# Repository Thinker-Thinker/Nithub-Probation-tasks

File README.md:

# Nithub-Probation-tasks
Contains Solution to NitHub Hardware Probation Tasks

author: Jokomba Quyum Adeola (THINKER)

Design and assemble a circuit using Arduino or Raspberry Pi to control an LED strip based on ambient light levels (use an LDR sensor).
Develop a PCB design (using KiCad or Eagle) for a temperature sensor module that communicates with the central hub.
Write firmware for an ESP32 to send sensor data (temperature, humidity) to a cloud server via MQTT.
Implement a security feature using a PIR motion sensor to trigger an alarm when motion is detected.
Optimize power consumption for a battery-powered IoT device by implementing sleep modes.

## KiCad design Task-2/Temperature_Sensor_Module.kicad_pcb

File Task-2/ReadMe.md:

Task 2 files

Develop a PCB design (using KiCad or Eagle) for a temperature sensor module that communicates with the central hub.

https://www.tinkercad.com/things/jzLXpQLUGEQ-nithub-task-2-

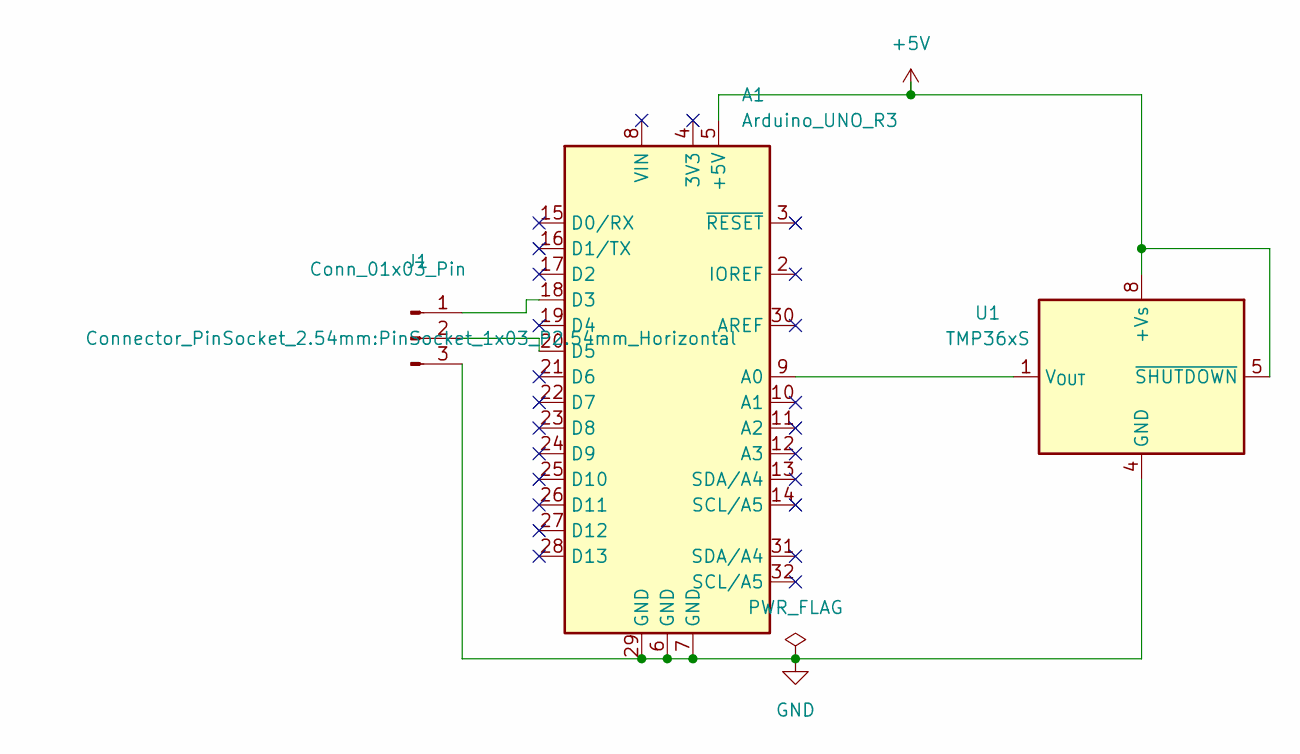
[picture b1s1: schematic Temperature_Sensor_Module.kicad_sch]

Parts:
A1: Arduino_UNO_R3
J1: Conn_01x03_Pin; PinSocket_1x03_P2.54mm_Horizontal
U1: TMP36xS; SOIC-8_3.9x4.9mm_P1.27mm

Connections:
+5V: A1.5 (+5V), U1.5 (~SHUTDOWN), U1.8 (+Vs)
GND: A1.6 (GND), A1.7 (GND), A1.29 (GND), J1.3, U1.4 (GND)
unnamed: A1.9 (A0), U1.1 (V_{OUT})
unnamed: A1.18 (D3), J1.1
unnamed: A1.20 (D5), J1.2

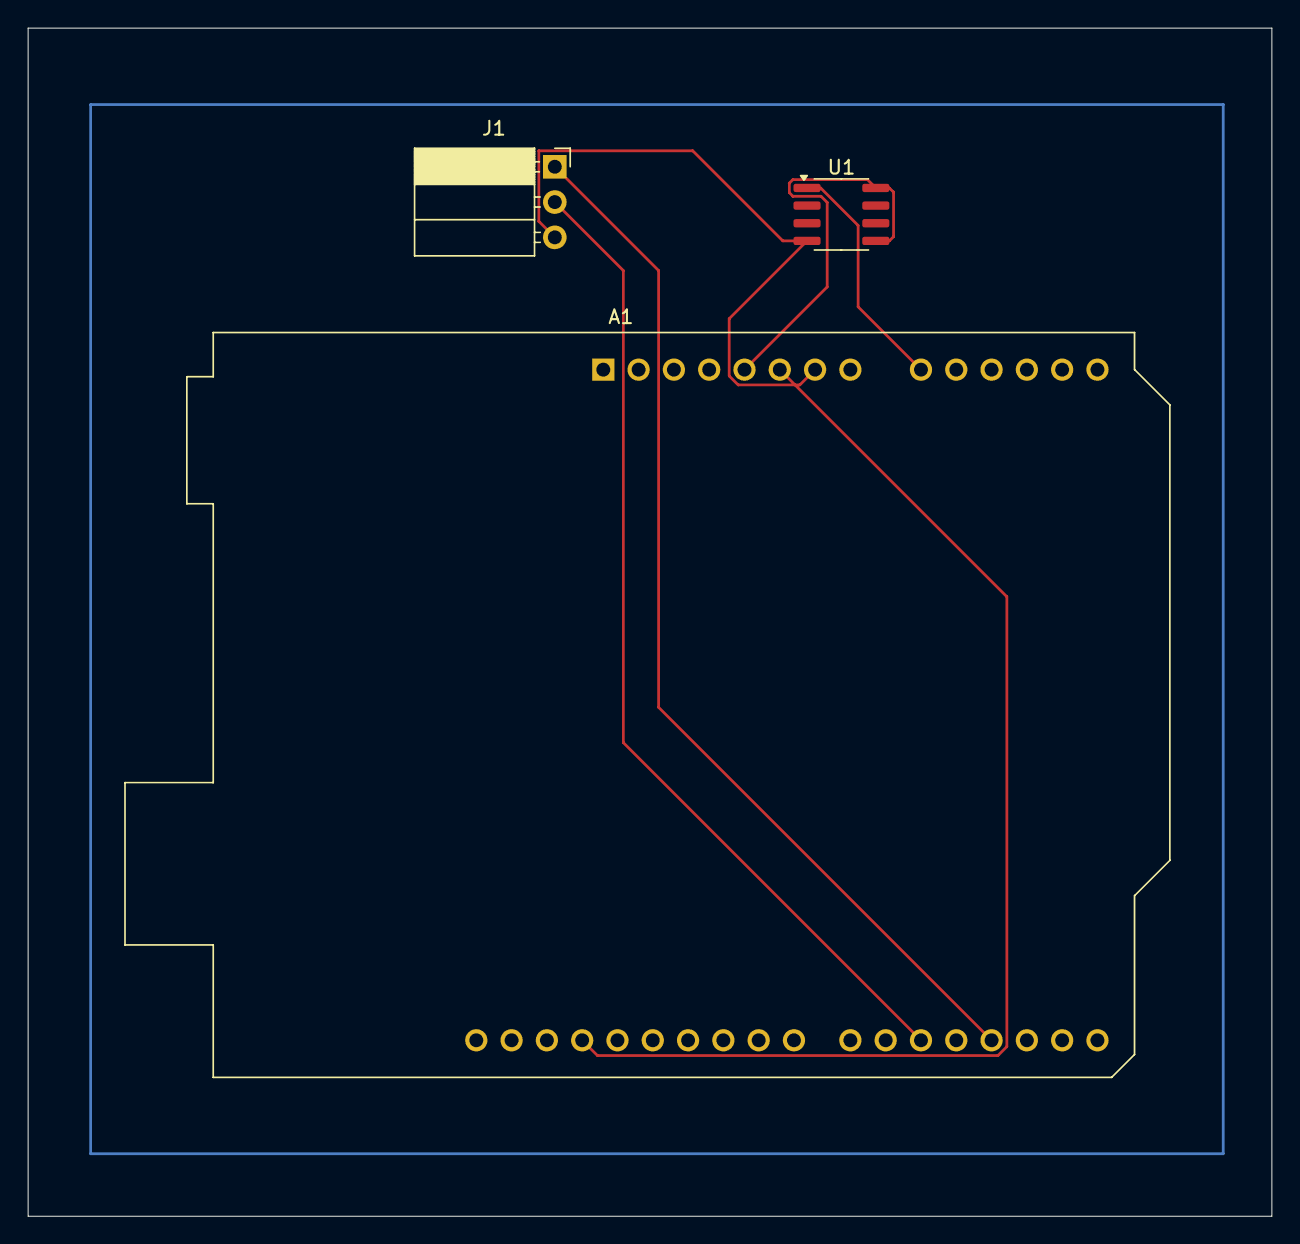
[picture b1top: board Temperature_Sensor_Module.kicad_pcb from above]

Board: 2 copper layers, 89.5 x 85.5 mm, 3 parts (0 on the bottom side), 5 nets.
